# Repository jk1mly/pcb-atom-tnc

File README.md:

# pcb-atom-tnc

M5 Atomモジュールを使用したFX.25対応TNCの基板
ハムフェア2023でPRUGブースにて展示＋少量頒布

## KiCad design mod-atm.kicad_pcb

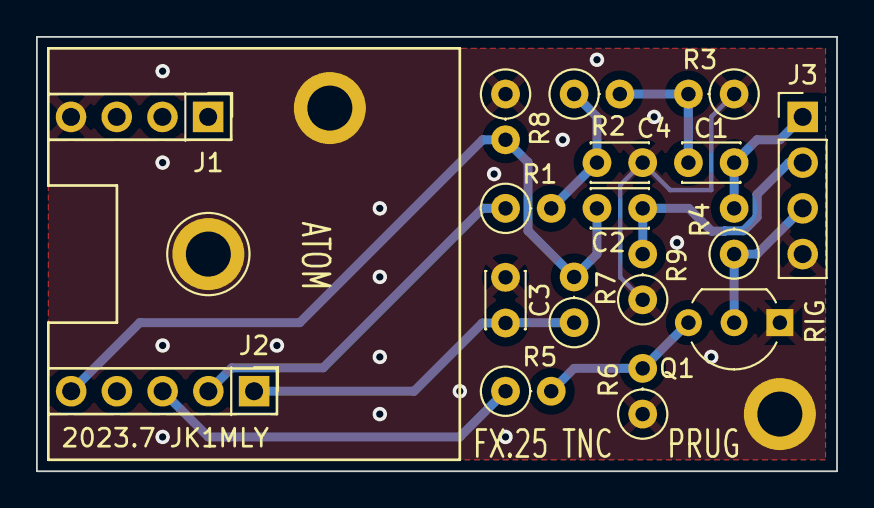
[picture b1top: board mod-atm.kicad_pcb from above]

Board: 2 copper layers, 44.4 x 24.1 mm, 20 parts (0 on the bottom side), 11 nets.

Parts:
C1, C2, C3, C4: C; C_Disc_D3.0mm_W2.0mm_P2.54mm
J1, J3: Conn_01x04_Socket; PinHeader_1x04_P2.54mm_Vertical
J2: Conn_01x05_Socket; PinHeader_1x05_P2.54mm_Vertical
Q1: 2SC1815; TO-92_Inline_Wide
R1, R2, R3, R4, R5, R6, R7, R8, R9: R; R_Axial_DIN0207_L6.3mm_D2.5mm_P2.54mm_Vertical
TP1, TP2, TP3: TestPoint; TestPoint_Plated_Hole_D3.0mm

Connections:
G19: J2.3, R5.1
G22: J2.2, R1.1
G33: C4.1, J2.5, R7.2, R8.2
GND: C2.2, C3.2, J1.4, J3.4, Q1.1 (E), R3.1, R6.1, R8.1, R9.1, TP1.1, TP2.1, TP3.1
MIC: C1.2, J3.1, R4.2
unnamed: C1.1, R2.2, R3.2
unnamed: C2.1, R1.2, R2.1
unnamed: Q1.3 (B), R5.2, R6.2
P3V: C3.1, J2.1, R7.1
PTT: J3.3, Q1.2 (C), R4.1
SPK: C4.2, J3.2, R9.2

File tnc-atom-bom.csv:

Reference,Value,Datasheet,num
C1,1u,P-15940,1
C2,0.1u,P-15940,1
C3,0.1u,P-15940,1
C4,1u,P-15940,1
J1,Conn_01x04_Socket,C-06631,1
J2,Conn_01x05_Socket,C-06631,1
J3,Conn_01x04_Socket,C-05779,1
Q1,2SC1815,I-06477,1
R1,220,R-25221,1
R2,4.7k,R-25472,1
R3,470,R-25471,1
R4,2.2k,R-25222,1
R4A,22k,R-25223,1
R5,4.7k,R-25472,1
R6,4.7k,R-25472,1
R7,100k,R-25104,1
R8,22k,R-25223,1
R9,15,R-25150,1
